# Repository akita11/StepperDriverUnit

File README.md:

# SteppterDriverUnit

ステッピングモータをGrove端子からの方向・パルスのみで制御できるUNITです。ドライバICはよく使われるDRV8825の互換IC(HR8255)を使用しており、マイクロステップ駆動も可能です。またイネーブル・リセットは別の端子から与えることもできます。

# 使用法（まずは使ってみる）

- 6pコネクタ（ネジ端子：基板裏面にシルク表記あり）に、ステッピングモータの電源(+12V等）とモータのA相・B相(各2本：計4本）のケーブルを接続します。
- Grove端子にマイコンなど(M5Stack等)を接続します（ここからの+5V給電が本体の動作に必要です）
- Grove端子の信号線(DIRとSTP)でモータの回転の向きとステップを制御します。DIR=0/1で回転方向を決定し（実際の回転方向がどちらが時計回りかはA相・B相の配線によって異なる）、STPの立ち上がり（0→1の変化)で1ステップ進みます。

Grove端子のピン配置（基板裏面にシルク表記あり）： STP/DIR/+5V/GND

# 使用法（詳細な設定など）

半固定抵抗（RV1）でモータの駆動電流を設定てきます。また動作異常時にはD1(Fault)が点灯します。

## 補助制御端子

- J2の2本をショートすると、ドライバICをdisable状態にしてモータの駆動をOFFにします。
- J3の2本をショートすると、ドライバICの内部状態をリセットします。
- CN2にもこの2本の信号線が引き出してあり、Grove端子をとりつけてマイコン等から制御することができます。このGrove端子のピン配置（基板裏面にシルク表記あり）： nEN/nRST/+5V/GND （nEN=0でドライバICがON、=1でOFF。nRST=0でドライバICをリセット、=1で通常動作）

## 駆動方法の設定

基板裏面の4つのソルダージャンパで、モータの駆動方法を設定できます。詳細はHR8825（またはDRV8825）のデータシートを参照してください。

- M0/M1/M2: マイクロステップの設定。（o=ショート、x=開放）

| M0 | M1 | M2 | マイクロステップ |
| -- | -- | -- | -- |
| x  | x  | x  | フルステップ |
| o  | x  | x  | 1/2ステップ |
| x  | o  | x  | 1/4ステップ |
| o  | o  | x  | 8 microステップ |
| x  | x  | o  | 16 microステップ |
| o  | x  | o  | 32 microステップ |
| x  | o  | o  | 32 microステップ |
| o  | o  | o  | 32 microステップ |

- Dcy: Decayモードの設定（G-中央間をショート=slow / V-中央間をショート=fast / ショートなし=mixed）

# Author

Junichi Akita (akita@ifdl.jp / @akita11)

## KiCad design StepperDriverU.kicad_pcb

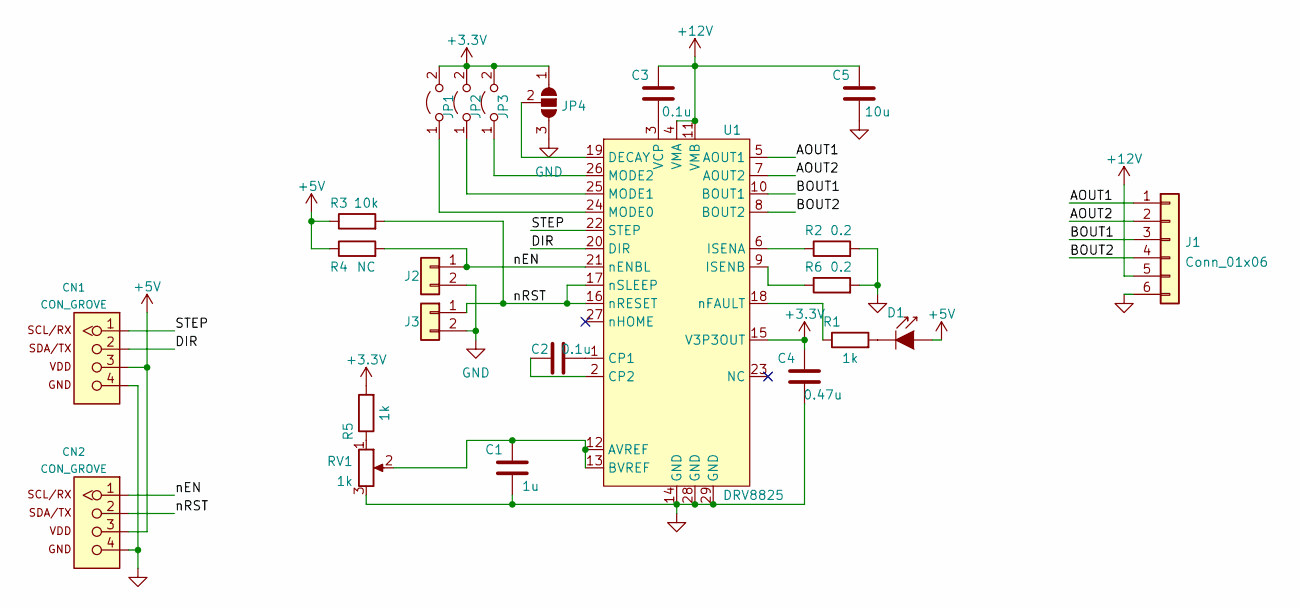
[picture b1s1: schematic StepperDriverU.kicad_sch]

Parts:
C1: 1u; C_0603_1608Metric
C2, C3: 0.1u; C_0603_1608Metric
C4: 0.47u; C_0603_1608Metric
C5: 10u; C_1206_3216Metric
CN1, CN2: CON_GROVE; CON_GROVE_H
D1: LED; LED_0603_1608Metric
J1: Conn_01x06; PinSocket_1x06_P2.54mm_Vertical
J2, J3: Conn_01x02; PinSocket_1x02_P2.54mm_Vertical
JP1, JP2, JP3: Jumper_2_Open; SolderJumper-2_P1.3mm_Open_Pad1.0x1.5mm
JP4: SolderJumper_3_Open; SolderJumper-3_P1.3mm_Open_Pad1.0x1.5mm
R1, R5: 1k; R_0603_1608Metric
R2, R6: 0.2; R_0805_2012Metric
R3: 10k; R_0603_1608Metric
R4: NC; R_0603_1608Metric
RV1: 1k; Potentiometer_Bourns_TC33X_Vertical
U1: DRV8825; HTSSOP-28-1EP_4.4x9.7mm_P0.65mm_EP2.85x5.4mm_ThermalVias

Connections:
+3V3: C4.2, JP1.2 (B), JP2.2 (B), JP3.2 (B), JP4.1 (A), R5.2, U1.15 (V3P3OUT)
+5V: CN1.3, CN2.3, D1.2 (A), R3.1, R4.1
+12V: C3.2, C5.2, J1.5, U1.4 (VMA), U1.11 (VMB)
/AOUT1: J1.1, U1.5 (AOUT1)
/AOUT2: J1.2, U1.7 (AOUT2)
/BOUT1: J1.3, U1.10 (BOUT1)
/BOUT2: J1.4, U1.8 (BOUT2)
/DIR: CN1.2, U1.20 (DIR)
/STEP: CN1.1, U1.22 (STEP)
/nEN: CN2.1, J2.1, R4.2, U1.21 (nENBL)
/nRST: CN2.2, J3.1, R3.2, U1.16 (nRESET), U1.17 (nSLEEP)
GND: C1.1, C4.1, C5.1, CN1.4, CN2.4, J1.6, J2.2, J3.2, JP4.3 (B), R2.2, R6.2, RV1.3, U1.14 (GND), U1.28 (GND), U1.29 (GND)
unnamed: C1.2, RV1.2, U1.12 (AVREF), U1.13 (BVREF)
unnamed: C2.1, U1.2 (CP2)
unnamed: C2.2, U1.1 (CP1)
unnamed: C3.1, U1.3 (VCP)
unnamed: D1.1 (K), R1.2
unnamed: JP1.1 (A), U1.24 (MODE0)
unnamed: JP2.1 (A), U1.25 (MODE1)
unnamed: JP3.1 (A), U1.26 (MODE2)
unnamed: JP4.2 (C), U1.19 (DECAY)
unnamed: R1.1, U1.18 (nFAULT)
unnamed: R2.1, U1.6 (ISENA)
unnamed: R5.1, RV1.1
unnamed: R6.1, U1.9 (ISENB)

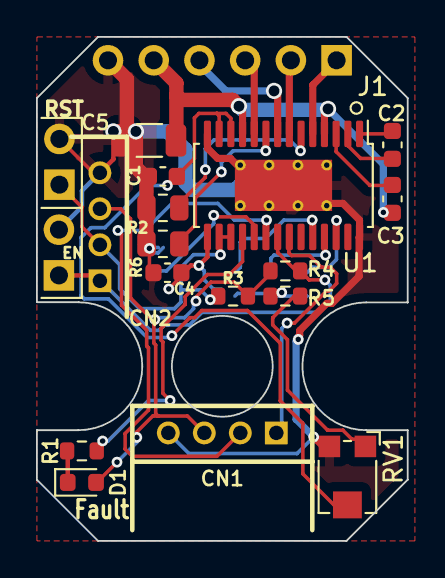
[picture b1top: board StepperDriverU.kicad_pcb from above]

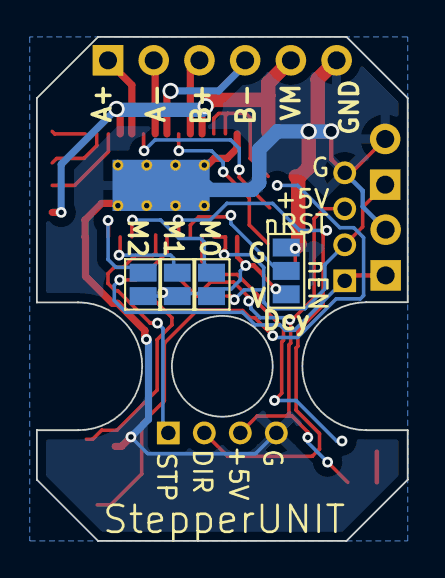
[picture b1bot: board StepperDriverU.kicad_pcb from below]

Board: 2 copper layers, 20.6 x 28.0 mm, 23 parts (4 on the bottom side), 25 nets.

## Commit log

2023-08-06 add photo
